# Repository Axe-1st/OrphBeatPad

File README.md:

# OrphBeatPad - A custom/open source Beat pad with awesome design!
## V2 IS OUT!! 

> PDF is available in Zine folder!

#### I wanted to make an custom beat pad that you can plug in into your computer and its good to go!
#### I would say the motivation was discovering FRS Sensors and bc i love hardware too much.
#### It Exists since i want to get started with making MIDI Stuff and see how much it can cost!
#### This project is basicaly a beat pad that can sense how hard are you tapping the pads and, BUT the most special part about this is it has integrated esp32-s3-wroom 1 🫣

#### Notes:
- The FSR Sensors Does not use a breakout board!
- There are Silicon pads that i will have to invividualy place to act as buttons!
- we will be ussing flush cutters so we can fit things nicely!
- We will use a combination of reflow and manual soldering.

### Schematic

#### New Schematic

### PCB 
#### look at that pcb 🤤

#### New PCB Design

### "pcb render"

#### New Version

- couldn't find a FSR sensor thats bent sorry!

### CAD

### Onshape Link https://cad.onshape.com/documents/ce0d6d23ca34879564001471/w/3b900ad8676028993156f6d1/e/086cec854ef049c97401a80d?renderMode=0&uiState=6a017598b3c539e8ea611fcd

#### i love onshape man

## How to build it
### a project thats been wating to be funded so it will relese soon!
#### But don't worry i can give you a rough idea how to make it!

- Step 1 Make sure all of your materials are ready such as (PCB, Stencil, Compoments, Hot Plate, 3D printed Case) if not don't worry as you can buy the compoments online from digikey and Jlcpcb! Check the BOM cause it has links!

- Step 2 Align the Stencil and spread solder Paste

- Step 3 Gently remove the stencil then place all of your compoments to reflow it at the hot plate! (you can use a soldering iron if you think you can do it!) a little tip when placing start from smallest to biggest!\

- Step 4 Reflow the board by making sure that the esp32 is in the middle! 

- Step 5 Now the Reflow is done start adding the compoments that need manual hand soldering, such as: Sk-mini-e, 16 channel Swicher, FSR sensor pads.

- Step 6 Your PCB is assembled! Final step is to assemble with the case! To assemble the case (3 parts) get the bottom and middle super glue it, then after drying place the pcb inside, also make sure the external pins are cut with a flush cutter! Add the top case then superglue it or Use any M4 thread screw.

- Step 7 Cut the Silicon Sheet into squares boxes then place it where the FSR Sensor holes are!

- Final step is to Plug in the USB C cable and hope no smoke comes out.. If none good job! Flash it with the firmware i have provided :)

- And thats your own OrphBeatpad! Enjoy tinkering with it!!

## Bill of materials
### check Bom.csv

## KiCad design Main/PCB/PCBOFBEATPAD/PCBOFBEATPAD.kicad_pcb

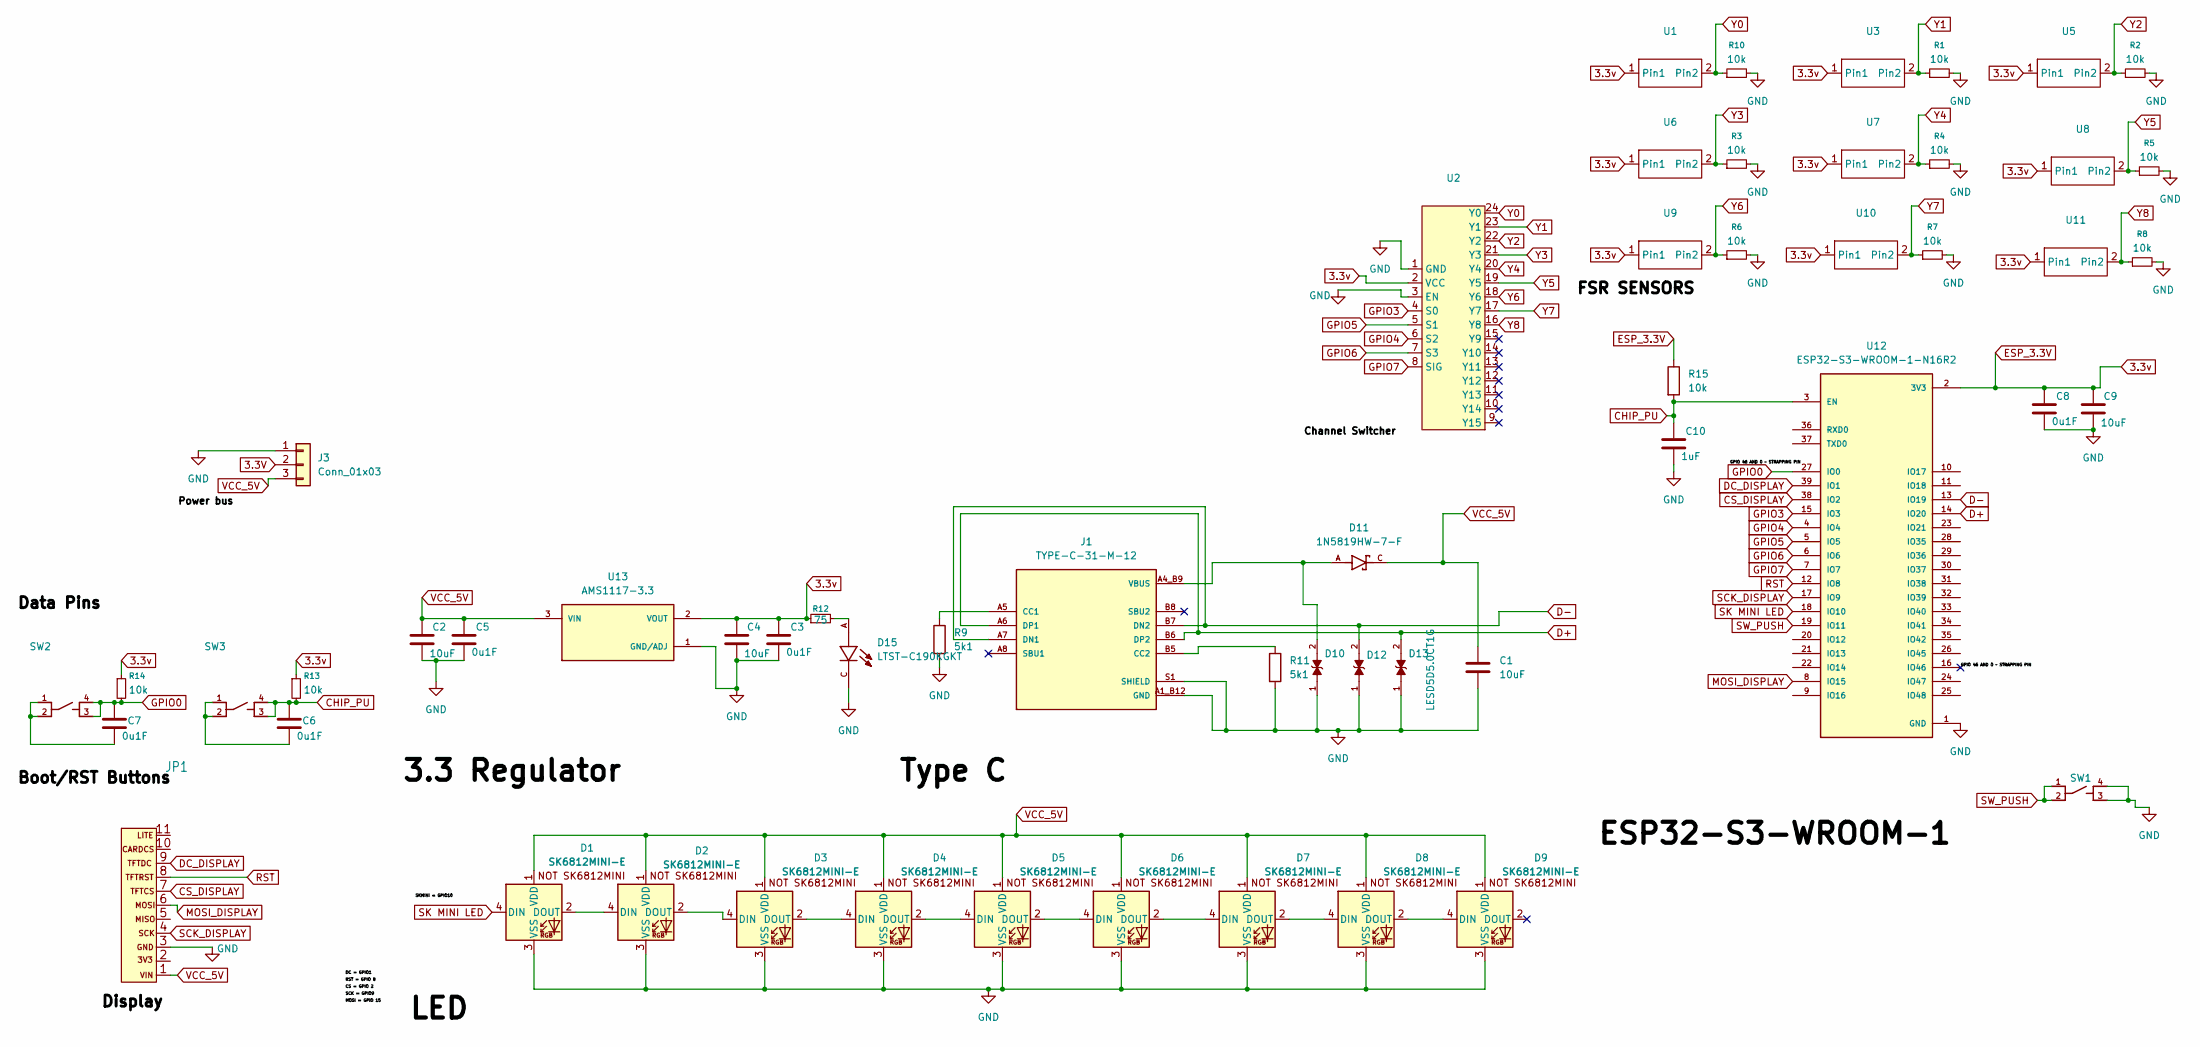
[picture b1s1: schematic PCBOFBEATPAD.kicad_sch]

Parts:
C1, C2, C4, C9: 10uF; C_0805_2012Metric_Pad1.18x1.45mm_HandSolder
C3, C5, C6, C7, C8: 0u1F; C_0805_2012Metric_Pad1.18x1.45mm_HandSolder
C10: 1uF; C_0805_2012Metric_Pad1.18x1.45mm_HandSolder
D1, D2, D3, D4, D5, D6, D7, D8, D9: SK6812MINI-E; SK6812MINI-E_fixed
D10, D12, D13: LESD5D5.0CT1G; TVS_LESD5D5.0CT1G; PARTREV O
D11: 1N5819HW-7-F; SOD3715X145N; PARTREV 18-2
D15: LTST-C190KGKT; LEDC1608X35N
J1: TYPE-C-31-M-12; HRO_TYPE-C-31-M-12; PARTREV 2020.12.08
J3: Conn_01x03; PinSocket_1x03_P2.00mm_Vertical
JP1: 1X11_ROUND_76
R1, R2, R3, R4, R5, R6, R7, R8, R10, R13, R14, R15: 10k; R_0603_1608Metric_Pad0.98x0.95mm_HandSolder
R9, R11: 5k1; R_0805_2012Metric_Pad1.20x1.40mm_HandSolder
R12: 75; R_0805_2012Metric_Pad1.20x1.40mm_HandSolder
SW1, SW2, SW3: PTS810_SJM_250_SMTR_LFS; SW_PTS810_SJM_250_SMTR_LFS
U1, U3, U5, U6, U7, U8, U9, U10, U11: 2 pin connector
U2: analog_16_multiplexer_module
U12: ESP32-S3-WROOM-1-N16R2; XCVR_ESP32-S3-WROOM-1-N16R2; PARTREV v1.0
U13: AMS1117-3.3; SOT229P700X180-4N; PARTREV N/A

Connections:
3.3V: J3.2
3.3v: C3.1, C4.1, C8.1, C9.1, R12.1, R13.1, R14.1, R15.1, U1.1 (Pin1), U2.2 (VCC), U3.1 (Pin1), U5.1 (Pin1), U6.1 (Pin1), U7.1 (Pin1), U8.1 (Pin1), U9.1 (Pin1), U10.1 (Pin1), U11.1 (Pin1), U12.2 (3V3), U13.2 (VOUT)
/GPIO 46 AND 0 ~ STRAPPING PIN: U12.16 (IO46)
CHIP_PU: C6.1, C10.1, R13.2, R15.2, SW3.3, SW3.4, U12.3 (EN)
CS_DISPLAY: JP1.7, U12.38 (IO2)
D+: D13.2, J1.A6 (DP1), J1.B6 (DP2), U12.14 (IO20)
D-: D12.2, J1.A7 (DN1), J1.B7 (DN2), U12.13 (IO19)
DC_DISPLAY: JP1.9, U12.39 (IO1)
GND: C1.2, C2.2, C3.2, C4.2, C5.2, C8.2, C9.2, C10.2, D1.3 (VSS), D2.3 (VSS), D3.3 (VSS), D4.3 (VSS), D5.3 (VSS), D6.3 (VSS), D7.3 (VSS), D8.3 (VSS), D9.3 (VSS), D10.1, D12.1, D13.1, D15.C, J1.A1_B12 (GND), J1.B1_A12 (GND), J1.S1 (SHIELD), J1.S2 (SHIELD), J1.S3 (SHIELD), J1.S4 (SHIELD), J3.1, JP1.3, R1.2, R2.2, R3.2, R4.2, R5.2, R6.2, R7.2, R8.2, R9.2, R10.2, R11.2, SW1.3, SW1.4, U2.1 (GND), U2.3 (EN), U12.1 (GND), U12.40 (GND), U12.41_1 (GND), U12.41_2 (GND), U12.41_3 (GND), U12.41_4 (GND), U12.41_5 (GND), U12.41_6 (GND), U12.41_7 (GND), U12.41_8 (GND), U12.41_9 (GND), U13.1 (GND/ADJ)
GPIO0: C7.1, R14.2, SW2.3, SW2.4, U12.27 (IO0)
GPIO3: U2.4 (S0), U12.15 (IO3)
GPIO4: U2.6 (S2), U12.4 (IO4)
GPIO5: U2.5 (S1), U12.5 (IO5)
GPIO6: U2.7 (S3), U12.6 (IO6)
GPIO7: U2.8 (SIG), U12.7 (IO7)
MOSI_DISPLAY: JP1.6, U12.8 (IO15)
unnamed: C6.2, SW3.1, SW3.2
unnamed: C7.2, SW2.1, SW2.2
unnamed: D1.2 (DOUT), D2.4 (DIN)
unnamed: D2.2 (DOUT), D3.4 (DIN)
unnamed: D3.2 (DOUT), D4.4 (DIN)
unnamed: D4.2 (DOUT), D5.4 (DIN)
unnamed: D5.2 (DOUT), D6.4 (DIN)
unnamed: D6.2 (DOUT), D7.4 (DIN)
unnamed: D7.2 (DOUT), D8.4 (DIN)
unnamed: D8.2 (DOUT), D9.4 (DIN)
unnamed: D15.A, R12.2
unnamed: J1.A5 (CC1), R9.1
unnamed: J1.B5 (CC2), R11.1
RST: JP1.8, U12.12 (IO8)
SCK_DISPLAY: JP1.4, U12.17 (IO9)
SK MINI LED: D1.4 (DIN), U12.18 (IO10)
SW_PUSH: SW1.1, SW1.2, U12.19 (IO11)
VBUS: D10.2, D11.A, J1.A4_B9 (VBUS), J1.B4_A9 (VBUS)
VCC_5V: C1.1, C2.1, C5.1, D1.1 (VDD), D2.1 (VDD), D3.1 (VDD), D4.1 (VDD), D5.1 (VDD), D6.1 (VDD), D7.1 (VDD), D8.1 (VDD), D9.1 (VDD), D11.C, J3.3, JP1.1, U13.3 (VIN)
Y0: R10.1, U1.2 (Pin2), U2.24 (Y0)
Y1: R1.1, U2.23 (Y1), U3.2 (Pin2)
Y2: R2.1, U2.22 (Y2), U5.2 (Pin2)
Y3: R3.1, U2.21 (Y3), U6.2 (Pin2)
Y4: R4.1, U2.20 (Y4), U7.2 (Pin2)
Y5: R5.1, U2.19 (Y5), U8.2 (Pin2)
Y6: R6.1, U2.18 (Y6), U9.2 (Pin2)
Y7: R7.1, U2.17 (Y7), U10.2 (Pin2)
Y8: R8.1, U2.16 (Y8), U11.2 (Pin2)

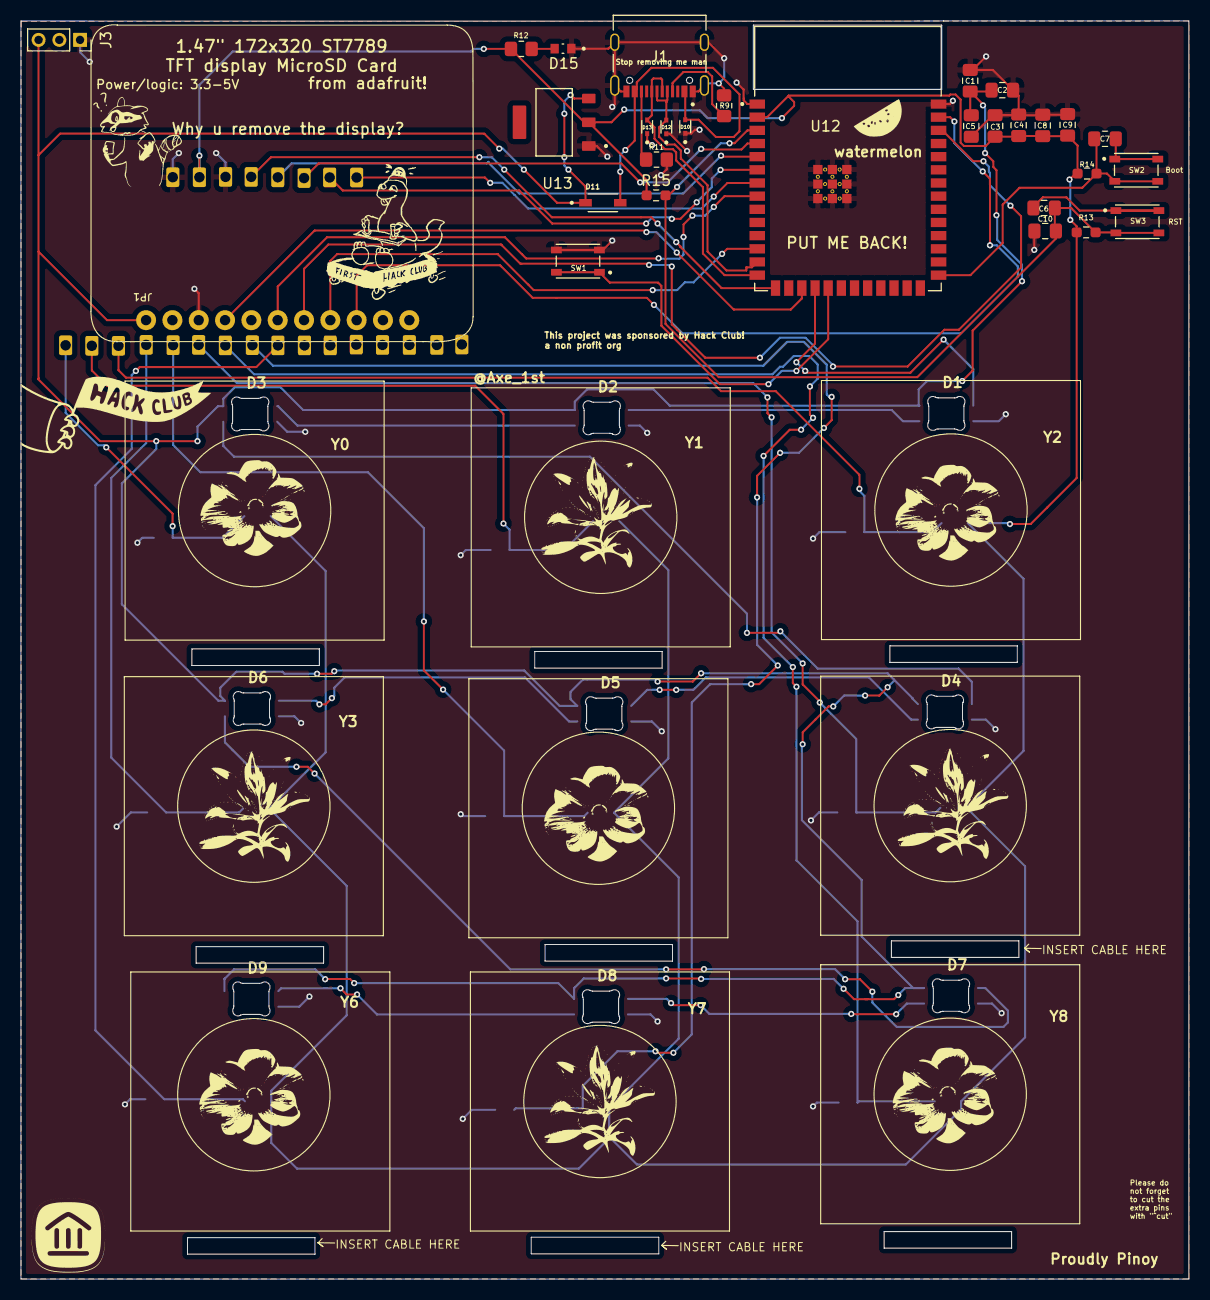
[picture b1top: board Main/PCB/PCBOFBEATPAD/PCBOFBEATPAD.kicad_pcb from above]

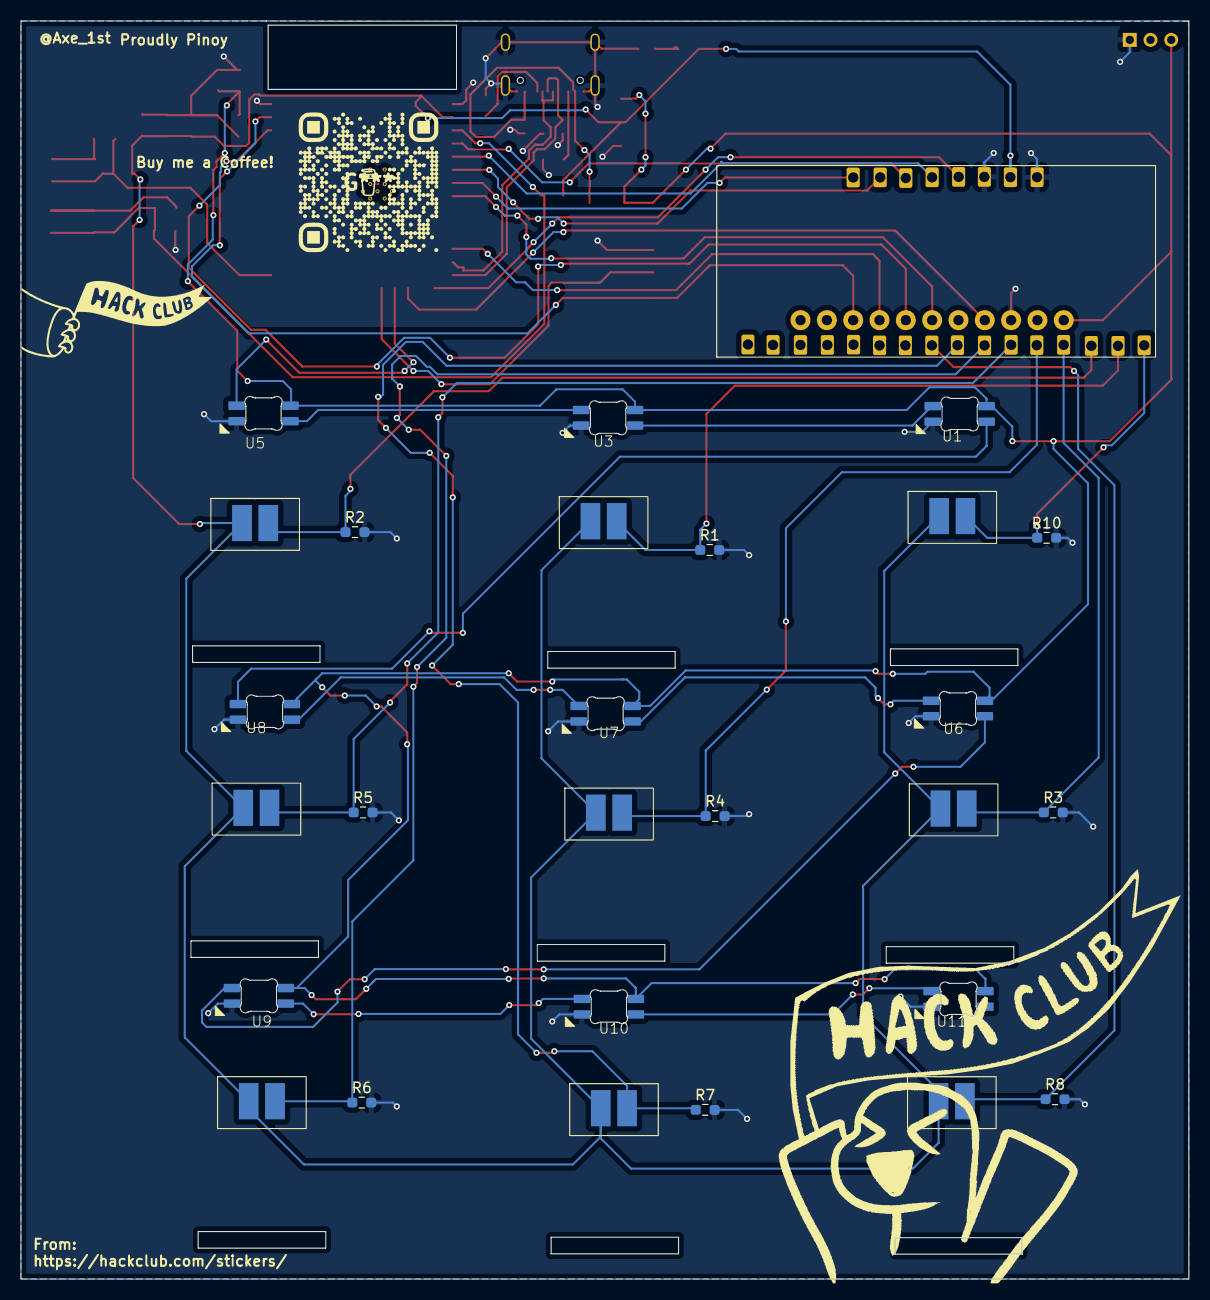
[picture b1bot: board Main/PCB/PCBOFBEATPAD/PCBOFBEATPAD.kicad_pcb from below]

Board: 2 copper layers, 112.7 x 121.4 mm, 57 parts (19 on the bottom side), 42 nets.

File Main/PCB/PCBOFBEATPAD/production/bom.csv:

Designator,Footprint,Quantity,Value,LCSC Part #
"C1, C2, C4, C9",0805,4,10uF,
C10,0805,1,1uF,
"C3, C5, C6, C7, C8",0805,5,0u1F,
"D1, D2, D3, D4, D5, D6, D7, D8, D9",SK6812MINI-E_fixed,9,SK6812MINI-E,
"D10, D12, D13",TVS_LESD5D5.0CT1G,3,LESD5D5.0CT1G,
D11,SOD3715X145N,1,1N5819HW-7-F,
D15,LEDC1608X35N,1,LTST-C190KGKT,
J1,HRO_TYPE-C-31-M-12,1,TYPE-C-31-M-12,
J3,PinSocket_1x03_P2.00mm_Vertical,1,Conn_01x03,
JP1,1X11_ROUND_76,1,~,
"R1, R10, R13, R14, R15, R2, R3, R4, R5, R6, R7, R8",0603,12,10k,
"R11, R9",0805,2,5k1,
R12,0805,1,75,
"SW1, SW2, SW3",SW_PTS810_SJM_250_SMTR_LFS,3,PTS810_SJM_250_SMTR_LFS,
"U1, U10, U11, U3, U5, U6, U7, U8, U9",2 pin connector,9,~,
U12,XCVR_ESP32-S3-WROOM-1-N16R2,1,ESP32-S3-WROOM-1-N16R2,
U13,SOT229P700X180-4N,1,AMS1117-3.3,
U2,analog_16_multiplexer_module,1,~,

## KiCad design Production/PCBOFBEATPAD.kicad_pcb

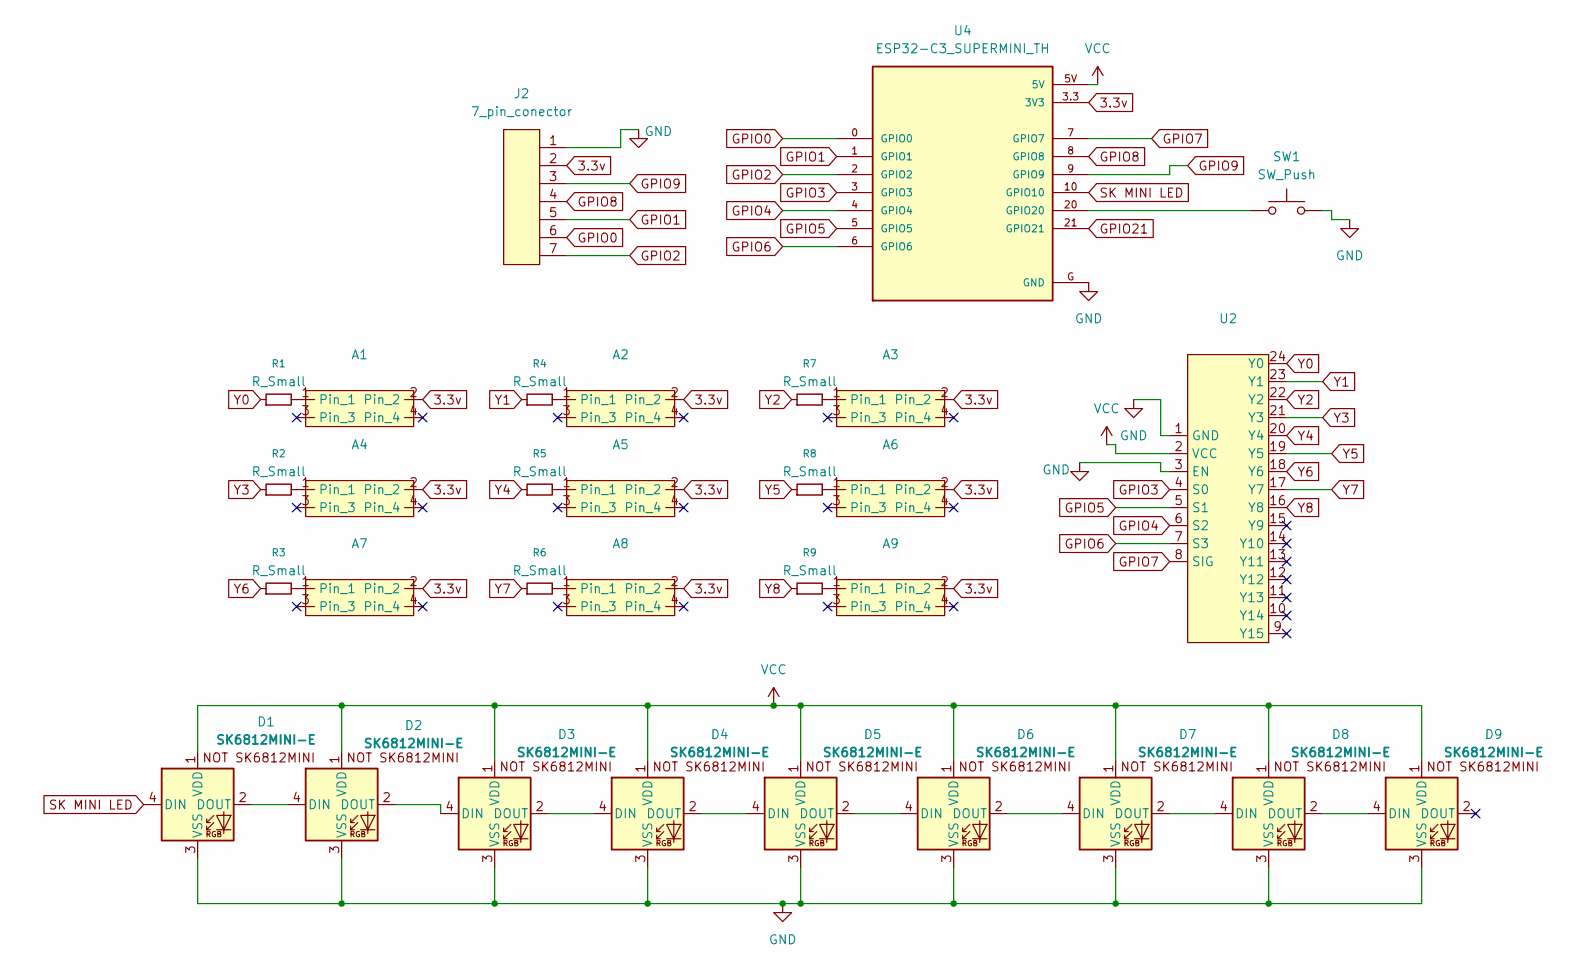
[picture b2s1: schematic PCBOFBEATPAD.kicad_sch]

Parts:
A1, A2, A3, A4, A5, A6, A7, A8, A9: 2x2 connectorss
D1, D2, D3, D4, D5, D6, D7, D8, D9: SK6812MINI-E; SK6812MINI-E_fixed
J2: 7_pin_conector; 1.3 tft display
R1, R2, R3, R4, R5, R6, R7, R8, R9: R_Small; R_Axial_DIN0204_L3.6mm_D1.6mm_P5.08mm_Horizontal
SW1: SW_Push; SW_PUSH_6mm
U2: analog_16_multiplexer_module
U4: ESP32-C3_SUPERMINI_TH; MODULE_ESP32-C3_SUPERMINI_TH

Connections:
3.3v: A1.2, A2.2, A3.2, A4.2, A5.2, A6.2, A7.2, A8.2, A9.2, J2.2, U4.3.3 (3V3)
GND: D1.3 (VSS), D2.3 (VSS), D3.3 (VSS), D4.3 (VSS), D5.3 (VSS), D6.3 (VSS), D7.3 (VSS), D8.3 (VSS), D9.3 (VSS), J2.1 (GND), SW1.2, U2.1 (GND), U2.3 (EN), U4.G (GND)
GPIO0: J2.6, U4.0 (GPIO0)
GPIO1: J2.5, U4.1 (GPIO1)
GPIO2: J2.7, U4.2 (GPIO2)
GPIO3: U2.4 (S0), U4.3 (GPIO3)
GPIO4: U2.6 (S2), U4.4 (GPIO4)
GPIO5: U2.5 (S1), U4.5 (GPIO5)
GPIO6: U2.7 (S3), U4.6 (GPIO6)
GPIO7: U2.8 (SIG), U4.7 (GPIO7)
GPIO8: J2.4, U4.8 (GPIO8)
GPIO9: J2.3, U4.9 (GPIO9)
GPIO21: U4.21 (GPIO21)
unnamed: A1.1, R1.2
unnamed: A2.1, R4.2
unnamed: A3.1, R7.2
unnamed: A4.1, R2.2
unnamed: A5.1, R5.2
unnamed: A6.1, R8.2
unnamed: A7.1, R3.2
unnamed: A8.1, R6.2
unnamed: A9.1, R9.2
unnamed: D1.2 (DOUT), D2.4 (DIN)
unnamed: D2.2 (DOUT), D3.4 (DIN)
unnamed: D3.2 (DOUT), D4.4 (DIN)
unnamed: D4.2 (DOUT), D5.4 (DIN)
unnamed: D5.2 (DOUT), D6.4 (DIN)
unnamed: D6.2 (DOUT), D7.4 (DIN)
unnamed: D7.2 (DOUT), D8.4 (DIN)
unnamed: D8.2 (DOUT), D9.4 (DIN)
unnamed: SW1.1, U4.20 (GPIO20)
SK MINI LED: D1.4 (DIN), U4.10 (GPIO10)
VCC: D1.1 (VDD), D2.1 (VDD), D3.1 (VDD), D4.1 (VDD), D5.1 (VDD), D6.1 (VDD), D7.1 (VDD), D8.1 (VDD), D9.1 (VDD), U2.2 (VCC), U4.5V
Y0: R1.1, U2.24 (Y0)
Y1: R4.1, U2.23 (Y1)
Y2: R7.1, U2.22 (Y2)
Y3: R2.1, U2.21 (Y3)
Y4: R5.1, U2.20 (Y4)
Y5: R8.1, U2.19 (Y5)
Y6: R3.1, U2.18 (Y6)
Y7: R6.1, U2.17 (Y7)
Y8: R9.1, U2.16 (Y8)

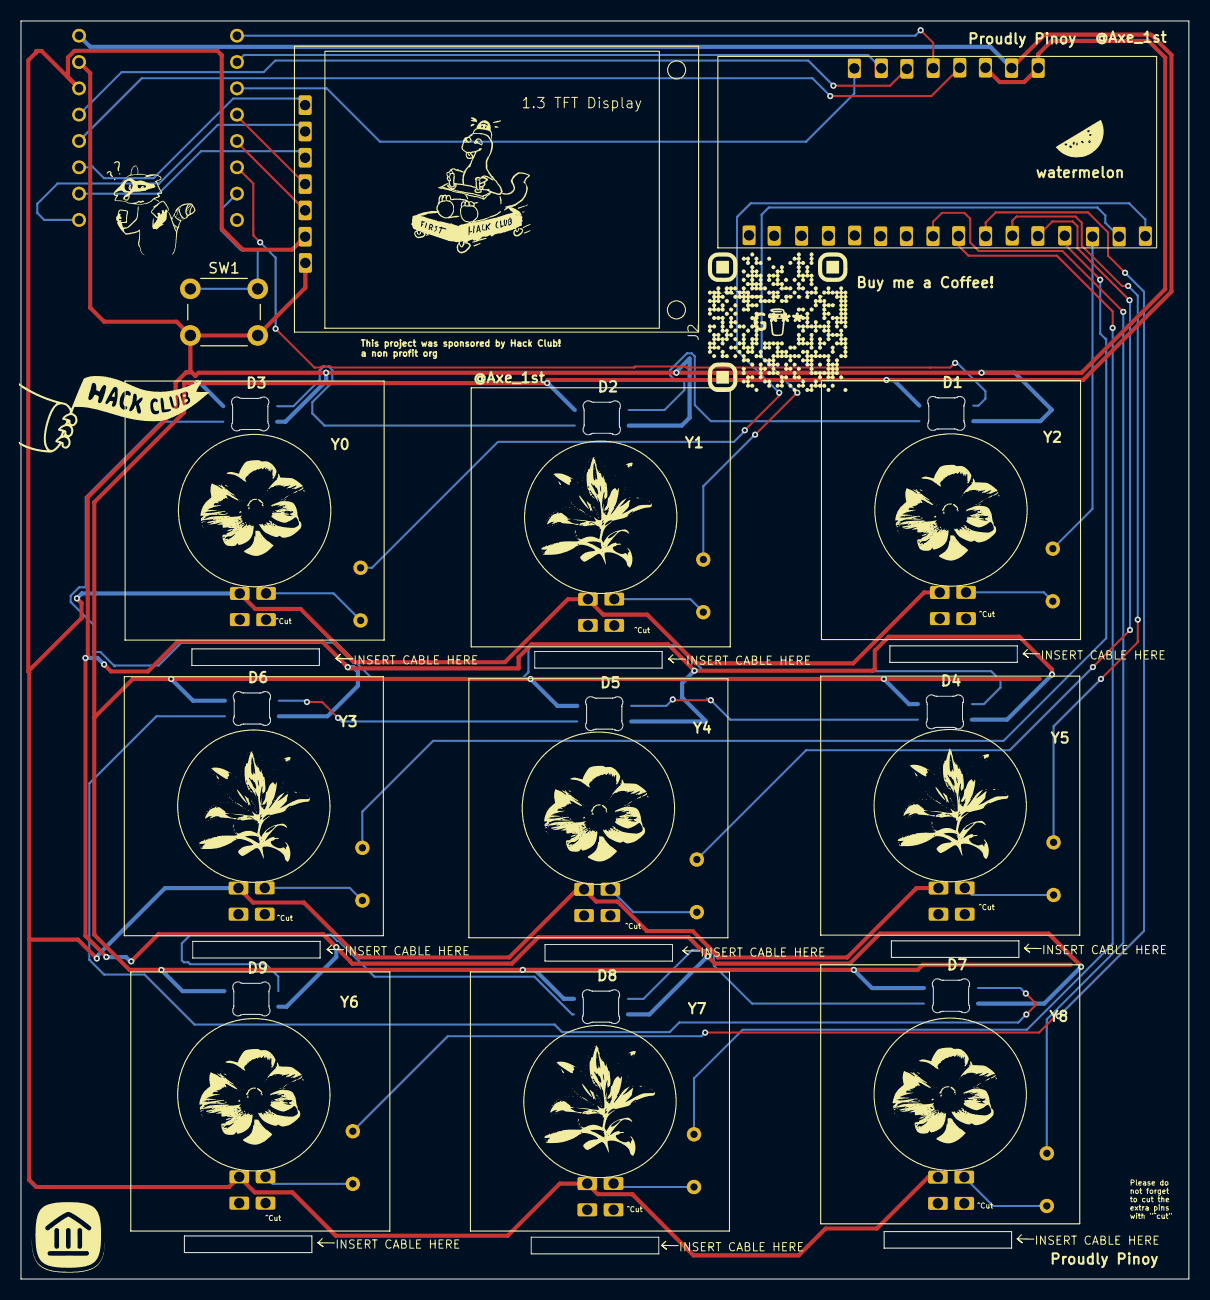
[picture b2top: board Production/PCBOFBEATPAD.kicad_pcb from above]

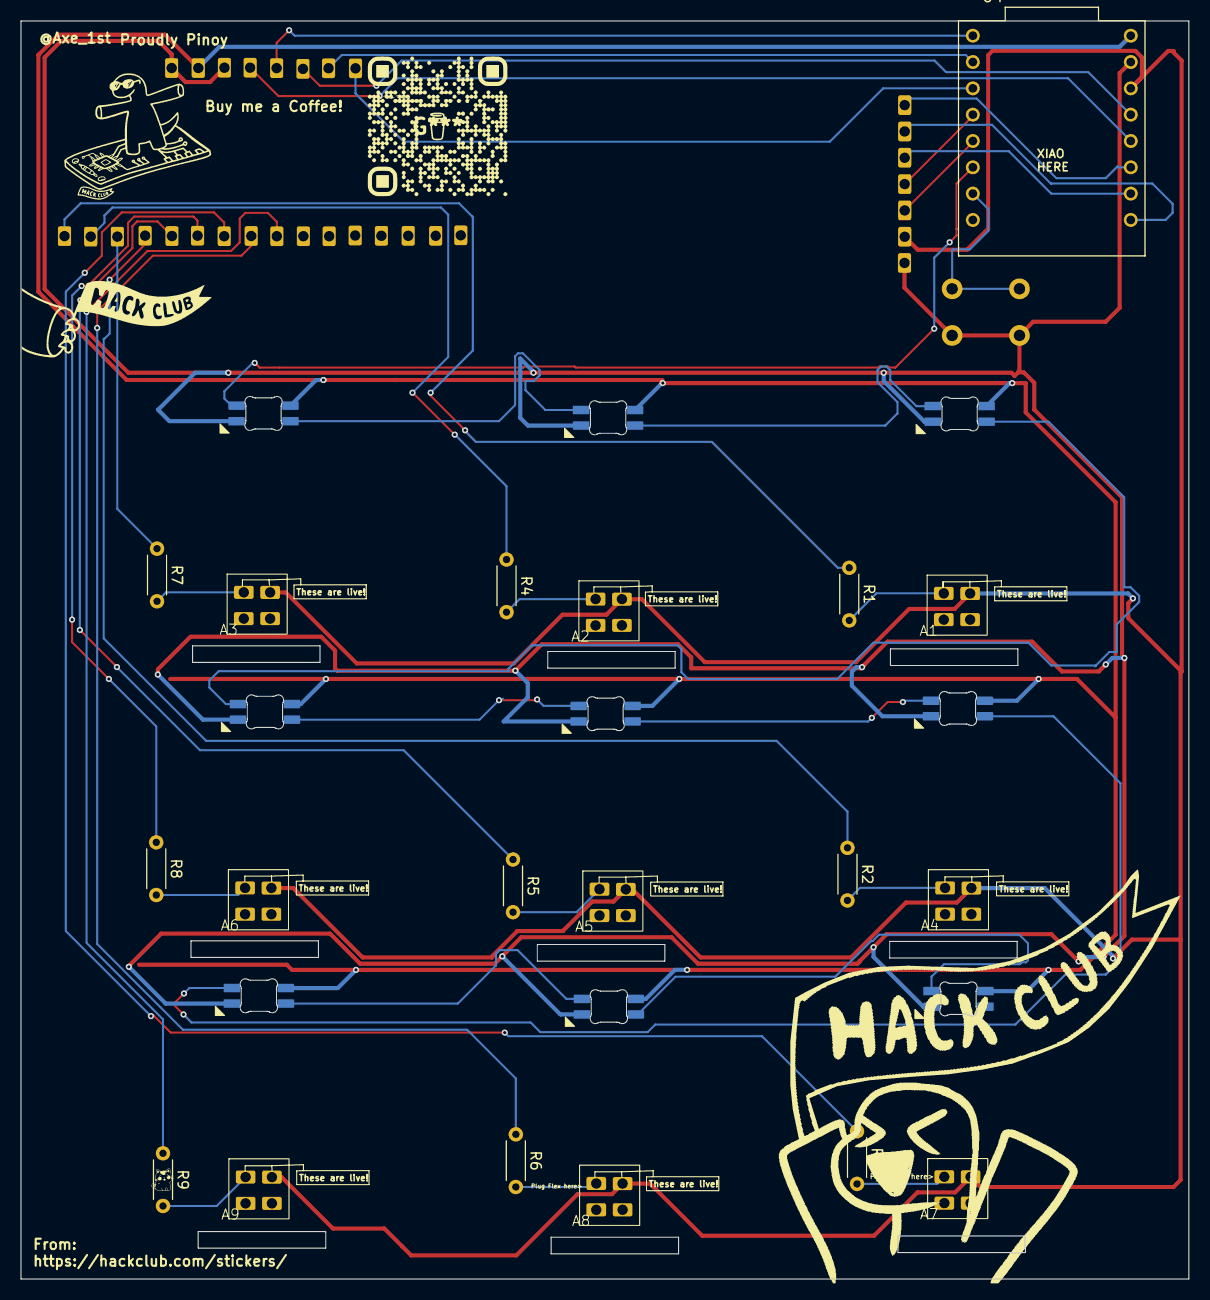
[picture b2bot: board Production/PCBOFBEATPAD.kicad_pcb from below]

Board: 2 copper layers, 112.7 x 121.4 mm, 31 parts (19 on the bottom side), 41 nets.

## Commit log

2026-04-01 Made first readme
    pls do not read me
2026-04-01 Added bom
2026-04-01 Adding Files to Github
    No Zine in this Version yet
2026-04-06 Zine Added
    Ahh at last my last commit
2026-04-06 Readme add zine pls thanks git love you git
2026-04-06 bom update
2026-04-06 Add Bill of Materials with component details
2026-04-06 Update jlcpcb pricing information in README
2026-04-06 Add 'How to build it' section to README
    Added a section on how to build the project.
2026-04-06 Added cad to main
2026-04-06 i hate ai checker slop
2026-04-06 Add CSV
2026-04-06 CSV of CSV
2026-04-06 Zine Fix
2026-05-08 update readme to V2
2026-05-08 Updated Readme
    OMDD the USB cad was flipped
2026-05-11 fix readme
2026-05-11 Added Onshape link and Cad image
2026-05-11 Major Update (V2 RELEASE)
2026-05-11 Add notes
2026-05-11 update pdf
2026-05-11 V2 IS OUT MAN
2026-05-11 Updated notes
2026-05-11 V2 final Commit
2026-05-11 v2 update
2026-05-11 Organized Repo
2026-05-11 Added How to make
2026-05-12 Fix zine Again!
2026-05-12 Updated Readme with instructions
2026-05-12 zine ahh update
2026-05-12 Debuging Zine
2026-05-12 Zine update
2026-05-12 Removed Backups!
2026-05-20 Update images in README for pcb render section
    Updated image dimensions and replaced an old image with a new one in the README.
2026-06-01 Update README with additional assembly instructions
    Added note about cutting silicon sheet for FSR sensors.
